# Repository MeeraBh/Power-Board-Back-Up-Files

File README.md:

# Power-Board-Back-Up-Files
Power Board Backup
A board that holds premade DC DC converters and has capacitors for power safety proportional to the in and expected out voltages and currents of the converters.  There are terminals to connect to the battery and pins out for connection to the rest of the system.  This is 1/3 PCBs for the system.

PCB:

3D View of PCB:

Old version of system.

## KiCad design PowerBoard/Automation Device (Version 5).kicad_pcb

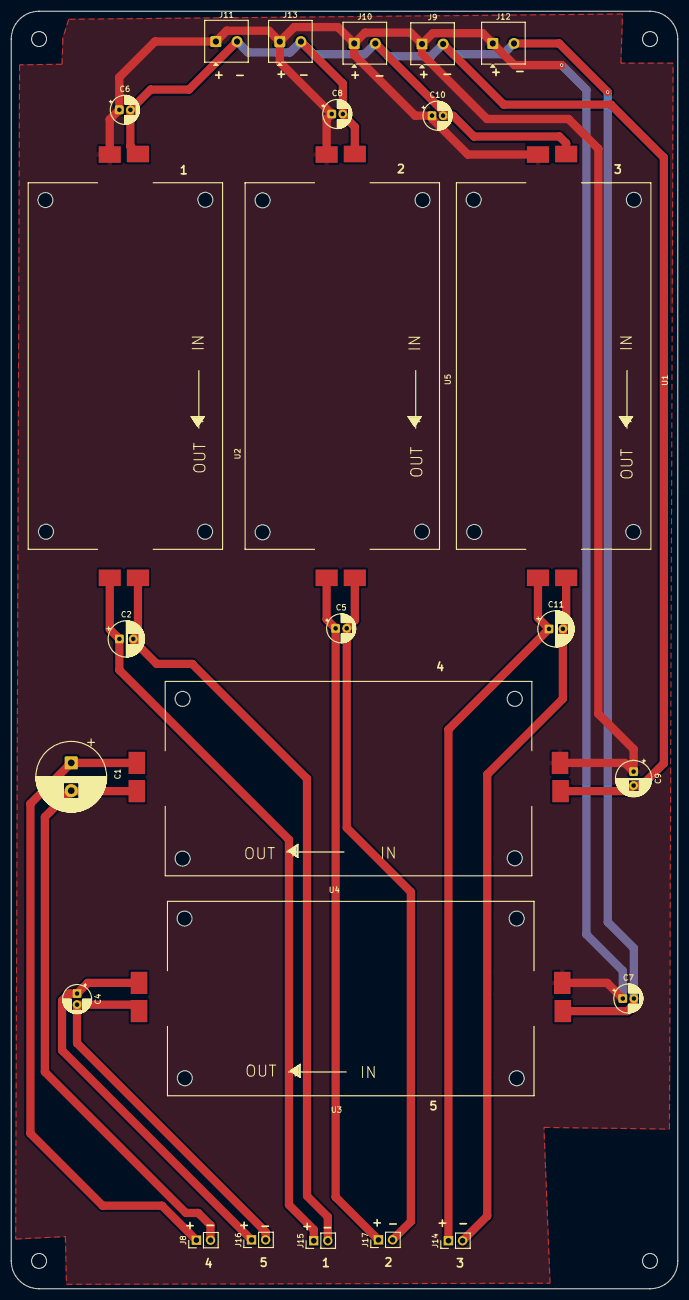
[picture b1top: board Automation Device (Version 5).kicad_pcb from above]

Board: 2 copper layers, 120.0 x 230.0 mm, 25 parts (0 on the bottom side), 12 nets.

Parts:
C1: C_Polarized_US (1000microF); CP_Radial_D12.5mm_P5.00mm
C2: C_Polarized_US (33microF); CP_Radial_D6.3mm_P2.50mm
C4, C5, C6, C7, C8, C10: C_Polarized_US (33microF); CP_Radial_D5.0mm_P2.00mm
C9, C11: C_Polarized_US (100microF); CP_Radial_D6.3mm_P2.50mm
J8, J14, J15, J16, J17: Conn_01x02_Pin; PinHeader_1x02_P2.54mm_Vertical
J9, J10, J11, J12, J13: Conn_01x02_Socket; TerminalBlock_Phoenix_MKDS-1-2-3.81_1x02_P3.81mm_Horizontal
U1: 24V -> 5V (Raspberry Pi); LM2596-DC-DC
U2, U5: 24V -> 3.3V (I2C Expander + Stepper Motors); LM2596-DC-DC
U3: 24V -> 5V (Servo + LED); LM2596-DC-DC
U4: 24V -> 10V (Peristaltc Pumps); LM2596-DC-DC

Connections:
+24V: C6.1, C7.1, C8.1, C9.1, C10.1, J9.1, J10.1, J11.1, J12.1, J13.1, U1.1 (+VDC), U2.1 (+VDC), U3.1 (+VDC), U4.1 (+VDC), U5.1 (+VDC)
GND: C6.2, C7.2, C8.2, C9.2, C10.2, J9.2, J10.2, J11.2, J12.2, J13.2, U1.3 (-VDC), U2.3 (-VDC), U3.3 (-VDC), U4.3 (-VDC), U5.3 (-VDC)
unnamed: C1.1, J8.1, U4.5 (VIN+)
unnamed: C1.2, J8.2, U4.7 (VIN-)
unnamed: C11.1, J14.1, U1.5 (VIN+)
unnamed: C11.2, J14.2, U1.7 (VIN-)
unnamed: C2.1, J15.1, U2.5 (VIN+)
unnamed: C2.2, J15.2, U2.7 (VIN-)
unnamed: C4.1, J16.1, U3.5 (VIN+)
unnamed: C4.2, J16.2, U3.7 (VIN-)
unnamed: C5.1, J17.1, U5.5 (VIN+)
unnamed: C5.2, J17.2, U5.7 (VIN-)
